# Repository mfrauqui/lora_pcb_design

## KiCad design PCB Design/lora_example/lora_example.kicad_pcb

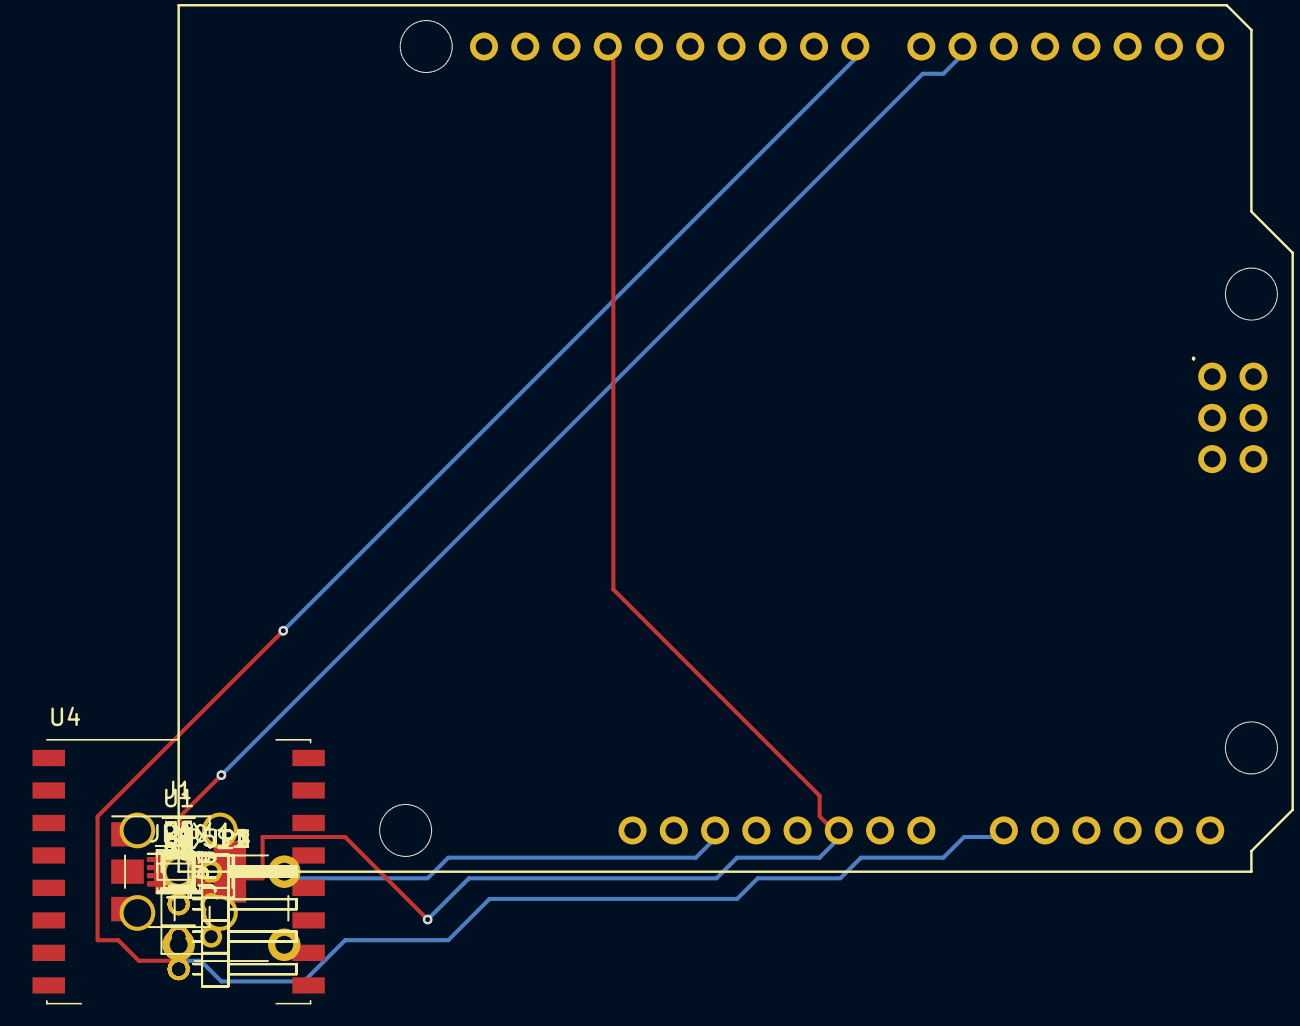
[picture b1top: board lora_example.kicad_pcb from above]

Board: 2 copper layers, 31 parts (0 on the bottom side), 35 nets.

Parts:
C1: 10uf; C_0805
C2: 22uf; C_0805
D1: 200mA; LED_0603
J1: COAX; SMA_THT_Jack_Straight
JP1: JP8; Pin_Header_Angled_1x04_Pitch2.00mm
JP2: JP9; Pin_Header_Angled_1x04_Pitch2.00mm
JP3: JP7; Pin_Header_Angled_1x04_Pitch2.00mm
JP4: JP10; Pin_Header_Angled_1x04_Pitch2.00mm
JP5: Arduino ICSP; Pin_Header_Straight_2x03_Pitch2.00mm
JP6: Arduino_Uno_Shield
JP7, JP8, JP9: Jumper; GS2
JP10: Conn_01x01; Pin_Header_Straight_1x01_Pitch2.54mm
Q1, Q2: BSS138; SOT-23
R1, R2, R3, R4, R8: 10K; R_0805
R5, R6, R7: 100R; R_0805
S1: Arduino Reset; SW_PUSH_6mm
U1: AP1117-33; SOT-223
U2, U3: 74LVC2G241; VSSOP-8_2.3x2mm_Pitch0.5mm
U4: RFM95 Lora Module; Hopref_RFM9XW_SMD
U5: 74LVC2G241; VSSOP-8_2.4x2.1mm_Pitch0.5mm
X1: Conn_Coaxial; CONN-RF-UFL

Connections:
/3V3_CS: U2.3, U4.5
/3V3_MISO: U3.5, U4.2
/3V3_MOSI: U3.6, U4.3
/3V3_SCK: U4.4, U5.6
/A0: JP1.4, JP6.A0
/A1: JP1.3, JP6.A1
/ARD_RST: JP6.RST1, S1.1
/CS: JP6.D10, U2.5
/D8: JP2.4, JP6.D8
/D9: JP2.3, JP6.D9
/DIO1: JP8.2, R6.2
/DIO2: JP7.2, R5.1
/INT: JP6.D2, R7.2
/LORA_RST: D1.1, R8.2, U4.6
/MISO: JP5.1, U3.3
/MOSI: JP5.4, U3.2
/SCK: JP5.3, U5.2
/SCL: JP3.4, JP6.SCL, Q2.3, R4.2
/SCL_V3: JP4.3, Q2.2, R2.2
/SDA: JP3.3, JP6.SDA, Q1.3, R3.2
/SDA_V3: JP4.4, Q1.2, R1.2
GND: C1.2, C2.2, J1.1, JP1.1, JP2.1, JP3.1, JP4.1, JP6.GND1, JP6.GND2, S1.2, U1.1, U2.4, U3.4, U4.1, U4.8, U4.10, U5.1, U5.4, X1.2
unnamed: C1.1, U1.3
unnamed: C2.1, U1.2
unnamed: D1.2, JP9.1
unnamed: J1.2, JP10.1, U4.9, X1.1
unnamed: JP6.D5, JP8.1
unnamed: JP6.D6, JP7.1
unnamed: JP6.D7, JP9.2
unnamed: Q1.1, Q2.1, R1.1, R2.1
unnamed: R3.1, R4.1
unnamed: R5.2, U4.16
unnamed: R6.1, U4.15
unnamed: R7.1, U4.14
unnamed: U2.7, U3.1, U3.7, U5.8

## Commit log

2018-05-04 mosquitto - added
2018-05-06 organized files and folders
